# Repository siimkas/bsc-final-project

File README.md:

# CAN Bus and CANopen Standard for Building and Home Automation, Analysis for Feasibility

Building and home automation is an essential part of energy efficiency efforts around the world. Wired and wireless communication protocols help implement the functionalities necessary for these automation systems. Because of the significant popularity increase in IoT solutions, wireless field-level protocols have been the main focus of development. Consequently, the adoption and development of wired fieldbus solutions have slowed down. Therefore, this thesis determines if CAN bus combined with CANopen standard is feasible for wired building and home automation to oﬀer a matured low-cost alternative for existing fieldbuses in the industry. The proposed wired solution could decrease the over-reliance on wireless technologies and complement those networks where possible. For this purpose, a proof-of-concept home automation system was developed using both custom-designed and commercial hardware with open-source software. The developed fieldbus network was additionally tested with a series of transmission tests to verify its performance. As a result, a CANopen fieldbus network was integrated into a well-known open-source IoT solution. Additionally, the underlying network performance was confirmed with some drawbacks noticed regarding the chosen microcontroller. This work presents the potential of CAN bus and CANopen standard in the context of building and home automation and justifies further research into the topic.

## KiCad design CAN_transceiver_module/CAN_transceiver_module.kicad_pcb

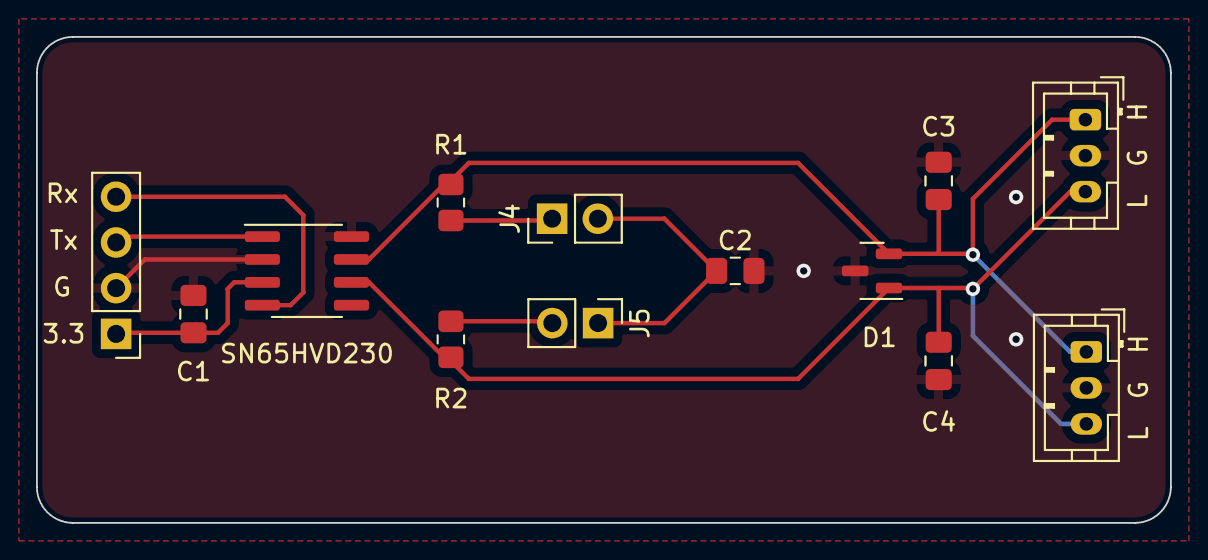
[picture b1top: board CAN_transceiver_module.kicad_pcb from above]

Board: 2 copper layers, 63.0 x 27.0 mm, 13 parts (0 on the bottom side), 9 nets.

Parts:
C1: 100nF; C_0805_2012Metric_Pad1.18x1.45mm_HandSolder
C2: 4.7nF; C_0805_2012Metric_Pad1.18x1.45mm_HandSolder
C3, C4: 100pF; C_0805_2012Metric_Pad1.18x1.45mm_HandSolder
D1: NUP2105L; SOT-23
J4, J5: Conn_01x02; PinHeader_1x02_P2.54mm_Vertical
L  G  H: Conn_01x03; JST_PH_B3B-PH-K_1x03_P2.00mm_Vertical
L  G  H#2: Conn_01x03; JST_PH_B3B-PH-K_1x03_P2.00mm_Vertical
R1, R2: 60; R_0805_2012Metric_Pad1.20x1.40mm_HandSolder
Rx: Conn_01x04; PinHeader_1x04_P2.54mm_Vertical
SN65HVD230: SN65HVD230; SOIC-8_3.9x4.9mm_P1.27mm

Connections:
/3.3V: C1.2, Rx.1, SN65HVD230.3 (VCC)
/CANH: C3.1, D1.2 (K), L G H.1, L G H#2.1, R1.1, SN65HVD230.7 (CANH)
/CANL: C4.2, D1.1 (K), L G H.3, L G H#2.3, R2.1, SN65HVD230.6 (CANL)
GND: C1.1, C2.2, C3.2, C4.1, D1.3 (A), L G H.2, L G H#2.2, Rx.2, SN65HVD230.2 (GND), SN65HVD230.8 (Rs)
unnamed: Rx.3, SN65HVD230.1 (D)
unnamed: Rx.4, SN65HVD230.4 (R)
unnamed: J4.1, R1.2
unnamed: C2.1, J4.2, J5.1
unnamed: J5.2, R2.2

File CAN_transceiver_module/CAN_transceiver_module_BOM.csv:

"Id";"Designator";"Footprint";"Quantity";"Designation";"Supplier and ref";
1;"L  G  H,L  G  H";"JST_PH_B3B-PH-K_1x03_P2.00mm_Vertical";2;"Conn_01x03";;;
2;"C2";"C_0805_2012Metric_Pad1.18x1.45mm_HandSolder";1;"4.7nF";;;
3;"D1";"SOT-23";1;"NUP2105L";;;
4;"C1";"C_0805_2012Metric_Pad1.18x1.45mm_HandSolder";1;"100nF";;;
5;"SN65HVD230";"SOIC-8_3.9x4.9mm_P1.27mm";1;"SN65HVD230";;;
6;"J4,J5";"PinHeader_1x02_P2.54mm_Vertical";2;"Conn_01x02";;;
7;"C4,C3";"C_0805_2012Metric_Pad1.18x1.45mm_HandSolder";2;"100pF";;;
8;"R2,R1";"R_0805_2012Metric_Pad1.20x1.40mm_HandSolder";2;"60";;;
9;"Rx";"PinHeader_1x04_P2.54mm_Vertical";1;"Conn_01x04";;;

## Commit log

2024-02-09 Draft 1 files
2024-02-22 Initial esphome config for nodes
2024-03-02 Configuration update and gateway.log
2024-03-03 Changes to transmission tests
2024-04-19 New transmission tests with results analysis
2024-04-27 Create LICENSE
